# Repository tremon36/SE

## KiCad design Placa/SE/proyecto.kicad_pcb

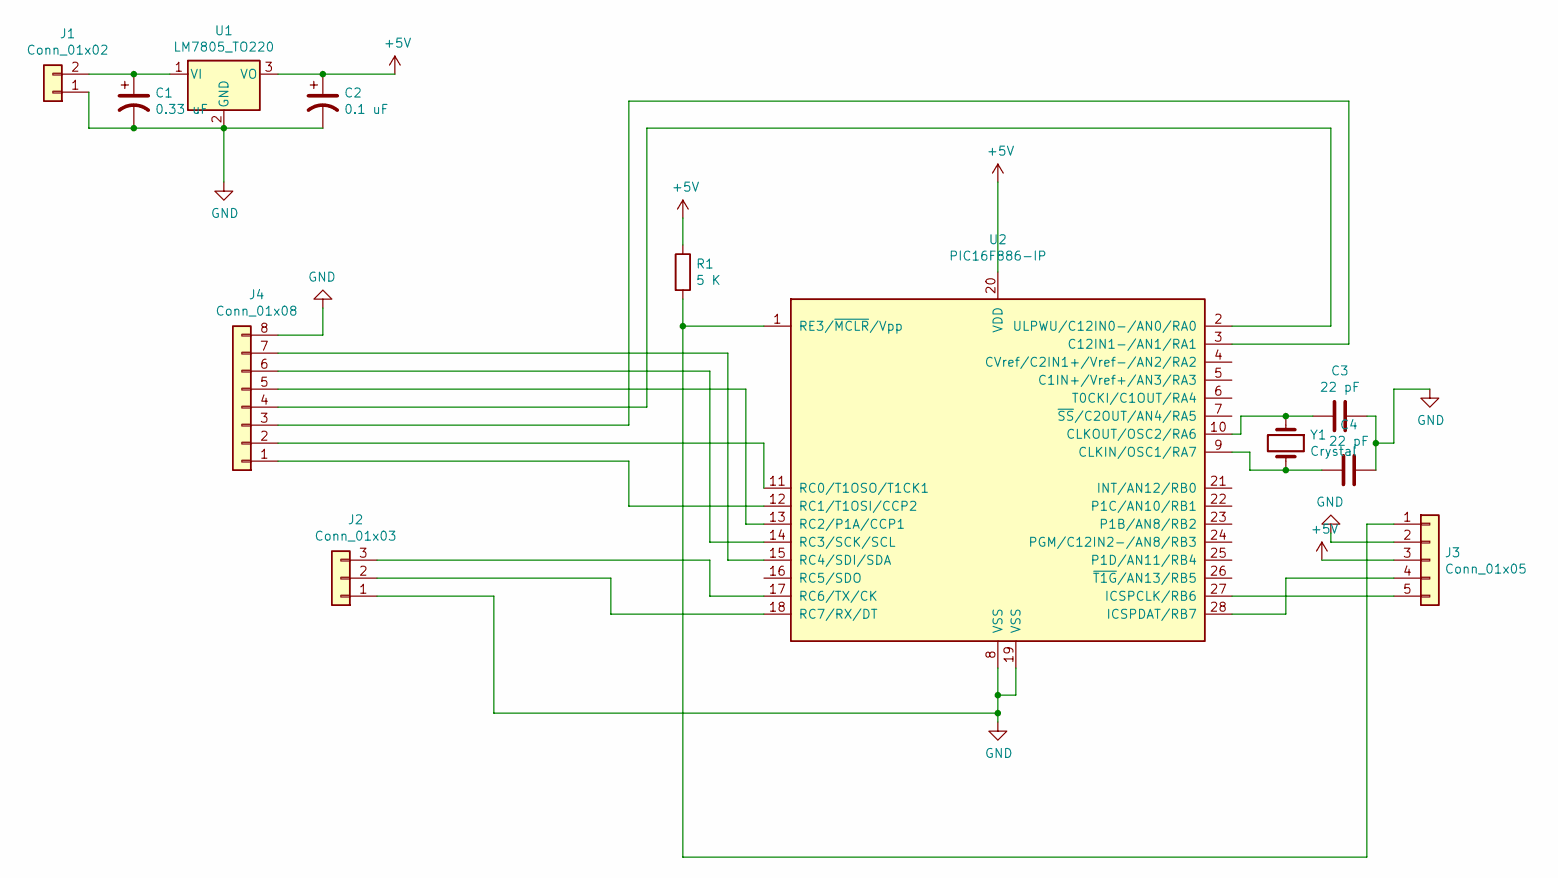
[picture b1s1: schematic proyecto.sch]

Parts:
C1: 0.33 uF; CP_Radial_D5.0mm_P2.50mm
C2: 0.1 uF; CP_Radial_D5.0mm_P2.50mm
C3, C4: 22 pF; C_Disc_D5.0mm_W2.5mm_P2.50mm
J1: Conn_01x02; TerminalBlock_bornier-2_P5.08mm
J2: Conn_01x03; PinHeader_1x03_P2.54mm_Vertical
J3: Conn_01x05; PinHeader_1x05_P2.54mm_Vertical
J4: Conn_01x08; PinHeader_1x08_P2.54mm_Vertical
R1: 5 K; R_Axial_DIN0207_L6.3mm_D2.5mm_P7.62mm_Horizontal
U1: LM7805_TO220; TO-220-3_Vertical
U2: PIC16F886-IP; DIP-28_W7.62mm_LongPads
Y1: Crystal; Crystal_HC18-U_Vertical

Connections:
+5V: C2.1, J3.3, R1.1, U1.3 (VO), U2.20 (VDD)
GND: C1.2, C2.2, C3.1, C4.1, J1.1, J2.1, J3.2, J4.8, U1.2 (GND), U2.8 (VSS), U2.19 (VSS)
unnamed: C1.1, J1.2, U1.1 (VI)
unnamed: C3.2, U2.10 (CLKOUT/OSC2/RA6), Y1.1
unnamed: C4.2, U2.9 (CLKIN/OSC1/RA7), Y1.2
unnamed: J2.2, U2.18 (RC7/RX/DT)
unnamed: J2.3, U2.17 (RC6/TX/CK)
unnamed: J3.1, R1.2, U2.1 (RE3/~MCLR~/Vpp)
unnamed: J3.4, U2.28 (ICSPDAT/RB7)
unnamed: J3.5, U2.27 (ICSPCLK/RB6)
unnamed: J4.1, U2.12 (RC1/T1OSI/CCP2)
unnamed: J4.2, U2.11 (RC0/T1OSO/T1CK1)
unnamed: J4.3, U2.3 (C12IN1-/AN1/RA1)
unnamed: J4.4, U2.2 (ULPWU/C12IN0-/AN0/RA0)
unnamed: J4.5, U2.13 (RC2/P1A/CCP1)
unnamed: J4.6, U2.14 (RC3/SCK/SCL)
unnamed: J4.7, U2.15 (RC4/SDI/SDA)

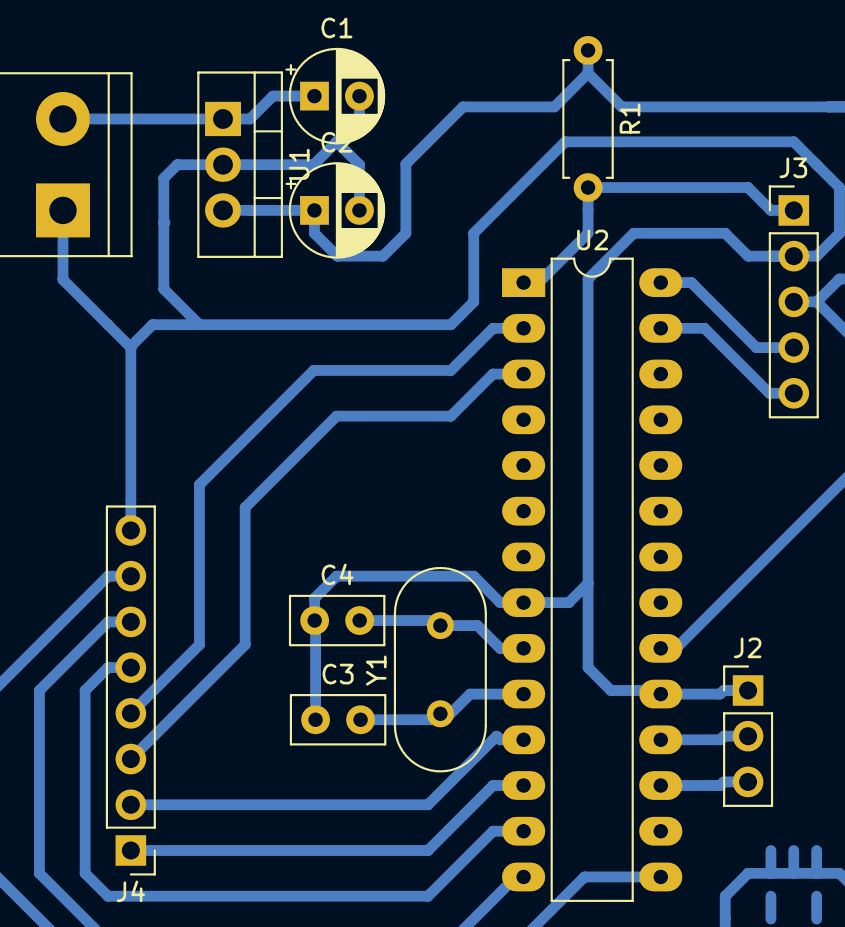
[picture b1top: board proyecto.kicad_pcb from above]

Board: 2 copper layers, 12 parts (0 on the bottom side), 17 nets.

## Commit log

2022-10-26 pwm added
2022-10-26 removed
2022-11-18 Placa v 1.0
2022-12-07 added lamp project
2022-12-07 project properties
2022-12-14 Usart task
2022-12-14 Actualizado el BRGH y SPBRG
2022-12-14 init SPI añadido
2022-12-21 Actulizado usart
